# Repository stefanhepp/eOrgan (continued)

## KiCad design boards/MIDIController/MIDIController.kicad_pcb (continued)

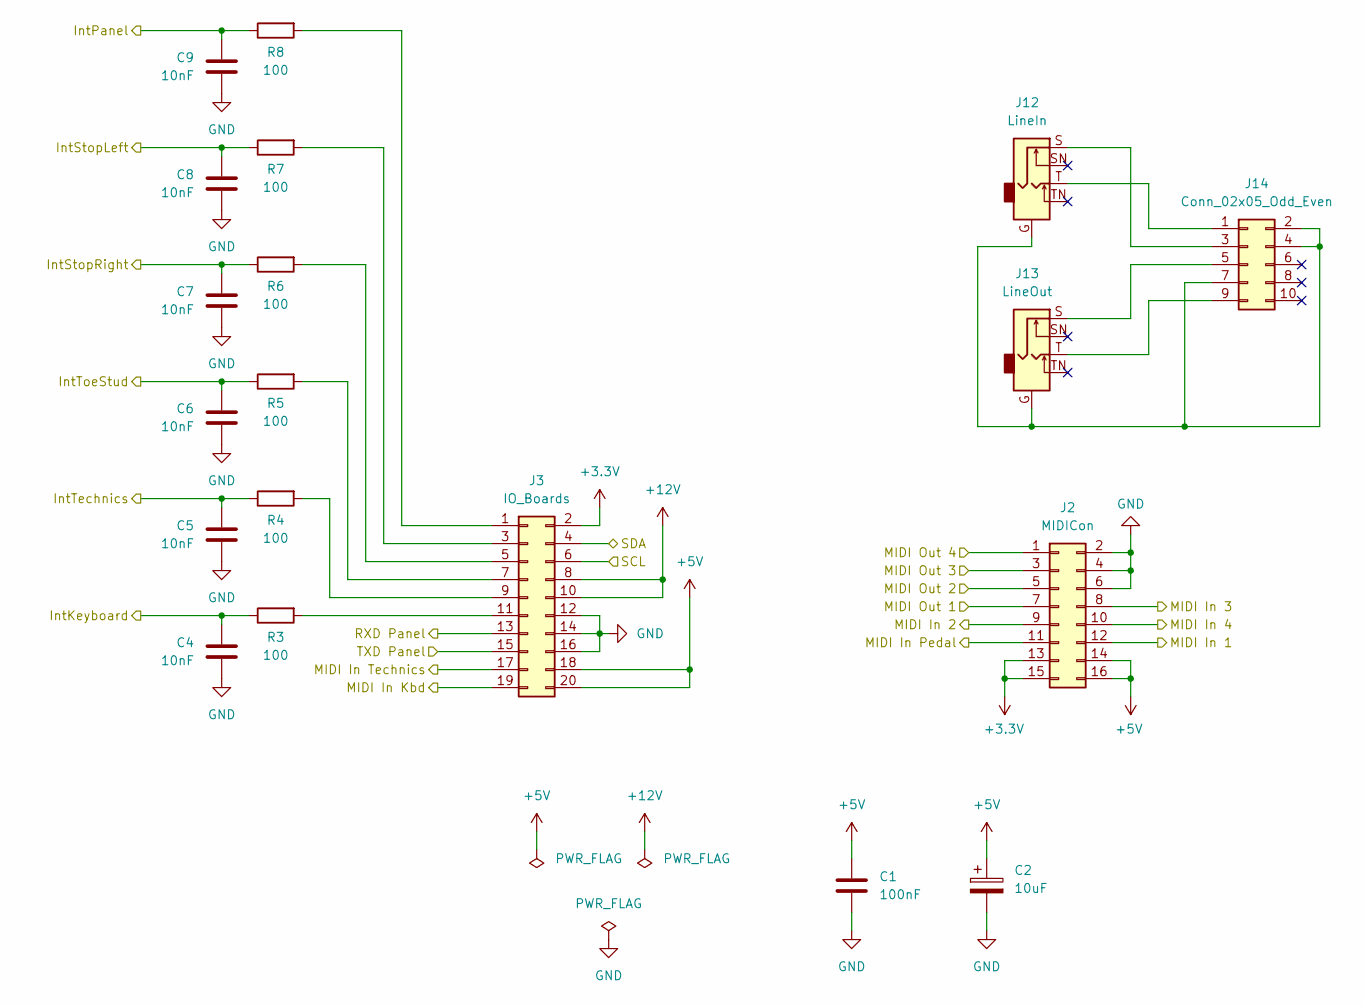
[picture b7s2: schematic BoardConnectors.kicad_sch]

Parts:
C1: 100nF; C_Disc_D4.3mm_W1.9mm_P5.00mm
C2: 10uF; CP_Radial_D5.0mm_P2.00mm
C4, C5, C6, C7, C8, C9: 10nF; C_Disc_D3.8mm_W2.6mm_P2.50mm
J2: MIDICon; IDC-Header_2x08_P2.54mm_Vertical
J3: IO_Boards; IDC-Header_2x10_P2.54mm_Vertical
J12: LineIn; Jack_3.5mm_Ledino_KB3SPRS_Horizontal_Stereo
J13: LineOut; Jack_3.5mm_Ledino_KB3SPRS_Horizontal_Stereo
J14: Conn_02x05_Odd_Even; PinHeader_2x05_P2.54mm_Vertical
R3, R4, R5, R6, R7, R8: 100; R_Axial_DIN0207_L6.3mm_D2.5mm_P10.16mm_Horizontal

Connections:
+3.3V: J2.13, J2.15, J3.2; also elsewhere on the board
+5V: C1.1, C2.1, J2.14, J2.16, J3.18, J3.20; also elsewhere on the board
+12V: J3.8, J3.10
/Int_Kbd: C4.1, R3.1; also elsewhere on the board
/Int_Panel: C9.1, R8.1; also elsewhere on the board
/Int_StopLeft: C8.1, R7.1; also elsewhere on the board
/Int_StopRight: C7.1, R6.1; also elsewhere on the board
/Int_Technics: C5.1, R4.1; also elsewhere on the board
/Int_ToeStud: C6.1, R5.1; also elsewhere on the board
/RXD1: J2.9; also elsewhere on the board
/RXD2: J3.19; also elsewhere on the board
/RXD3: J3.17; also elsewhere on the board
/RXD4: J2.10; also elsewhere on the board
/RXD5: J2.12; also elsewhere on the board
/RXD6: J3.13; also elsewhere on the board
/RXD7: J2.8; also elsewhere on the board
/RXD8: J2.11; also elsewhere on the board
/SCL: J3.6; also elsewhere on the board
/SDA: J3.4; also elsewhere on the board
/TXD1: J2.5; also elsewhere on the board
/TXD4: J2.1; also elsewhere on the board
/TXD5: J2.7; also elsewhere on the board
/TXD6: J3.15; also elsewhere on the board
/TXD7: J2.3; also elsewhere on the board
GND: C1.2, C2.2, C4.2, C5.2, C6.2, C7.2, C8.2, C9.2, J2.2, J2.4, J2.6, J3.12, J3.14, J3.16; also elsewhere on the board
unnamed: J3.1, R8.2
unnamed: J3.3, R7.2
unnamed: J3.5, R6.2
unnamed: J3.7, R5.2
unnamed: J3.9, R4.2
unnamed: J3.11, R3.2
unnamed: J12.T, J14.1
unnamed: J12.G, J13.G, J14.2, J14.4, J14.7
unnamed: J12.S, J14.3
unnamed: J13.S, J14.5
unnamed: J13.T, J14.9

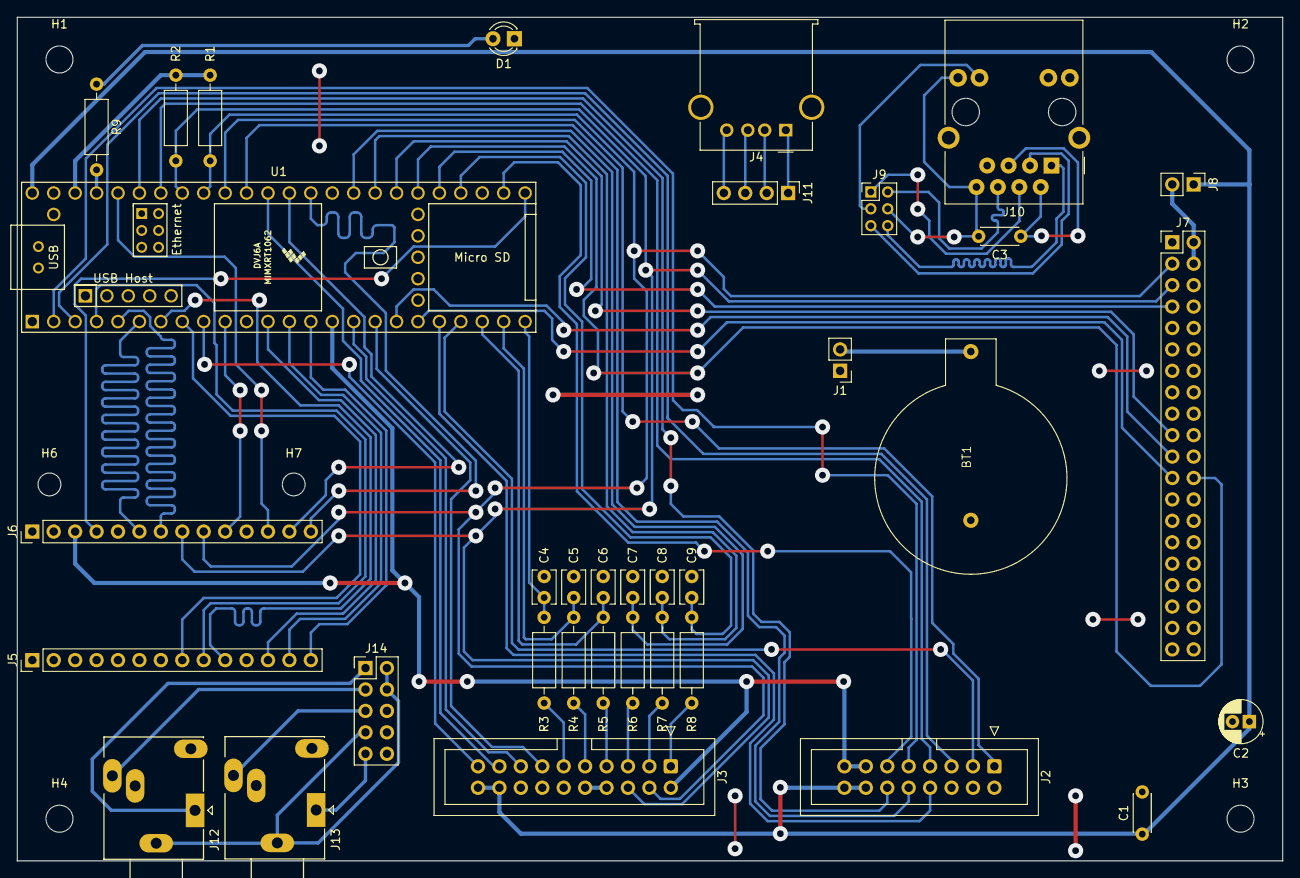
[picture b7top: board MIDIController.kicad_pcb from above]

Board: 2 copper layers, 150.0 x 100.0 mm, 41 parts (0 on the bottom side), 70 nets.

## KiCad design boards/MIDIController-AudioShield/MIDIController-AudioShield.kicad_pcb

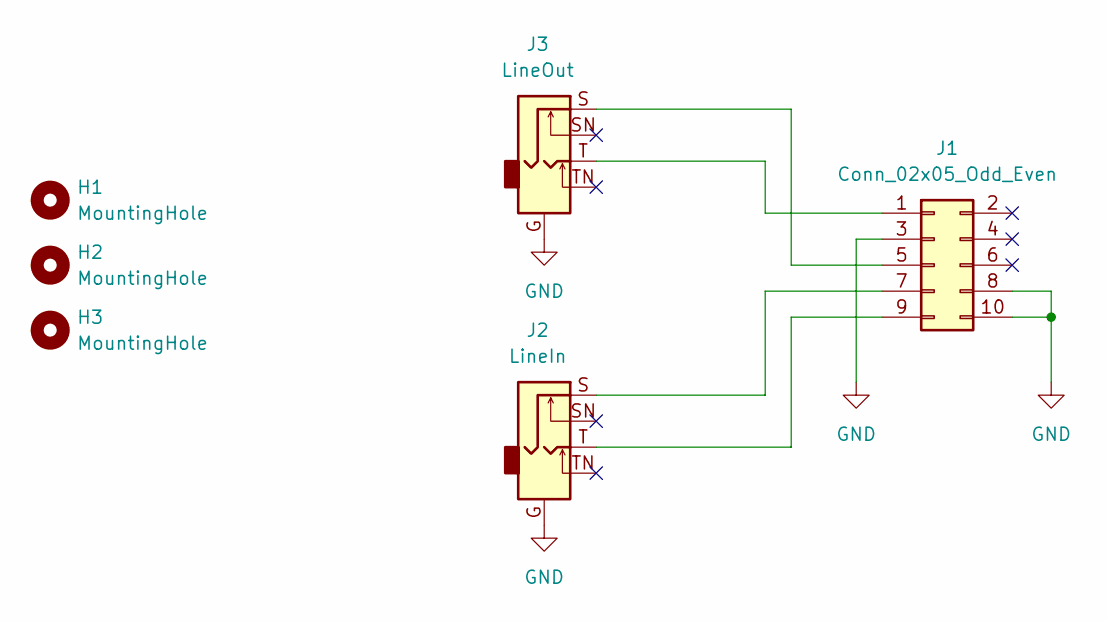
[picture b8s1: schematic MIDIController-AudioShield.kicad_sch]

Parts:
H1, H2, H3: MountingHole; MountingHole_3.2mm_M3
J1: Conn_02x05_Odd_Even; PinHeader_2x05_P2.54mm_Vertical
J2: LineIn; Jack_3.5mm_Ledino_KB3SPRS_Horizontal_Stereo
J3: LineOut; Jack_3.5mm_Ledino_KB3SPRS_Horizontal_Stereo

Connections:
GND: J1.3, J1.8, J1.10, J2.G, J3.G
unnamed: J1.1, J3.T
unnamed: J1.5, J3.S
unnamed: J1.7, J2.S
unnamed: J1.9, J2.T

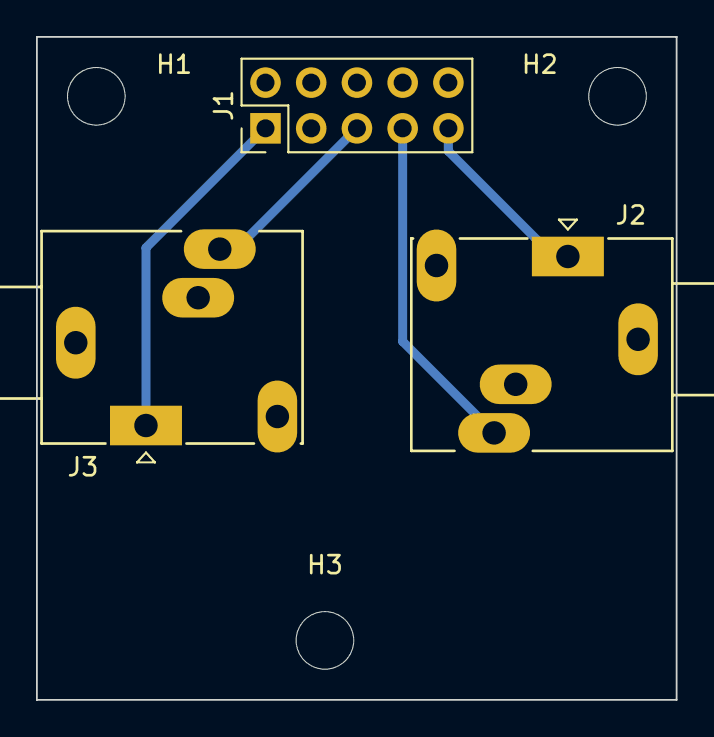
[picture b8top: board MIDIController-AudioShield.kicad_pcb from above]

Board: 2 copper layers, 35.5 x 36.8 mm, 6 parts (0 on the bottom side), 5 nets.

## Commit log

2013-10-13 Initial commit or encoder boards
2013-10-14 Added schematics of thumb pistons
2013-10-14 Fixed thumb piston wiring schematics
2013-10-14 First version of thumb encoder schematics
2013-10-15 Added first matrix encoder schematics, some design files
2013-10-15 Updated matrix encoder schematics
2022-09-15 Added old firmware and design files
2022-10-30 Initial design files for new Console design.
    Moved old design to archive folder, updated some documents for new
    design.
2022-11-13 New SwellEncoder schematics, updated MIDI paths in Boards diagram
2022-11-19 Added Freecad files for toestop switch holder and button boxes
2022-12-17 Updated 3D printed part designs and added STL exports
2022-12-17 Added Boutique retention hook design from https://www.thingiverse.com/thing:2430610
2022-12-17 Fixed Boutique retention hook design to fit Roland SE-02
2022-12-17 Renamed toestud encoder schematics
2022-12-17 Renamed toe stud connectors
2022-12-17 Renamed encoder boards and recreated with KiCAD 6
2022-12-18 Added schematics of pedal board controller
2022-12-18 Some updates to piston encoder schematics
2022-12-20 Updated Pedal Encoder to use UART from ToeStudEncoder
2022-12-20 Added Keyboard encoder and Midi encoder design using shift registers
2022-12-20 Finished Piston encoder schematics
2022-12-21 Updated keyboard encoder to use 8-1 Mux instead of shift registers
2022-12-21 Annoted ICs
2022-12-21 Added base schematics for Technics keyboard encoder
2022-12-21 Updated Board overview diagrams for new keyboard encoders
2022-12-21 Added initial schematics for main controller board
2023-02-22 Moved firmware sources to separate repository
2023-02-22 Using Creative Commons 4.0 ShareAlike license for hardware design
2023-02-22 Fixed readme formatting
2023-04-17 Remove temporary and local KiCAD files
2023-04-19 Renamed PCBs and updated to KiCAD 7.0
2023-04-19 Moved individual part designs into subfolder
2023-04-23 Created new signals drawings
2023-10-21 Added Audio/MIDI routes diagram
2023-10-21 PCB layout for keyboard scanner and piston encoder
2024-01-13 Ignore new freecad backup files
2024-01-13 Added redesigned Roland Boutique holder
2024-02-07 Added Audio frontpanel, added more MIDI ports to controller
2024-02-13 Added output buffer to MIDI outputs
2024-03-04 Updated to KiCAD 8, fixed optocouplers for MIDI and added powersupplies
2024-03-04 New PCB version of PedalEncoder
2024-03-05 Using custom TO220 cooler, fixed and finished several PCBs
2024-03-05 Finished PCB for ToeStudEncoder
2024-03-06 Cleanup of PCB sizes and mounthole positions. Moved MIDI connectors to separate board.
2024-03-06 Finished PCB for MIDI IO board
2024-03-07 Added Optocoupler and RS232 converter to UART board lines.
2024-03-08 Finished IO-Board PCB, switched RX/TX of board connectors for better routing
2024-03-08 Finished connectors on MIDIController board, fixed 3.3V IO voltage levels
2024-03-08 Updated MidiController PCB footprints
2024-03-11 Fixed interrupt line to use open collector, added pullups to I2C lines
2024-03-11 Added CR2032 holder footprint, allow routing between pins
2024-03-13 Added bypass caps to power supplies, use cheaper MAX232 IC.
2024-05-18 Updated design rules to 0.32mm template and exported Gerber files
2024-06-16 Fixed some RX/TX pin swaps
2024-06-16 Initial firmware commands doc
2024-06-17 Added notes on MIDI and I2C routing and opcodes
2024-06-26 Fixed size of I2C expander board footprint
2024-06-30 Added PCB holder model
2024-06-30 Make Toestud PS2 connectors symmetrical to avoid connection errors
2024-06-30 Added case for ToeStudEncoder
2024-06-30 ToeStudEncoder: Fixed mirrored PS2 pinout
2024-06-30 Added slide-in holder for ToeStudEncoder case
2024-07-03 Fixed mirrored MIDI board connector
2024-07-04 Updated I2C protocol
2024-07-10 Fixed Piston wiring schematics, updated I2C message formats
2024-07-21 Added software architecture overview for MIDIcontroller
2024-07-21 Updated I2C message formats
2024-07-23 Updated I2C message formats and SW arhitecture
2024-08-03 Fixed PedalEncoder ISP hedaer schematics, added Errata notes
2024-08-05 Fixed PedalEncoder ISP connections
2024-08-18 Moved firmware docs to eOrgan-firmware repo
2024-08-30 Fixed KeyboardScanner schematics to fix open collector enable output
2024-08-31 Revert "Fixed KeyboardScanner schematics to fix open collector enable output"
    This reverts commit 57decbb2314c6d76a4ad6cd92ca682e4977913ef.
2024-08-31 Replaced inverting with non-inverting output buffer in KeyboardScanner to fix disabled open collector output
2024-08-31 Reverting to using 2803A inverted open collector for Keyboard Scanner, fixed layout
2024-09-02 Added IDC16 connector workaround, PCB holder for TechnicsEncoder
2024-09-02 Added LED controller board
2024-09-07 Exported LEDController gerber
2024-09-07 Parametric design for PCB holder
2024-09-07 Fixed LEDController button header layout
2024-09-13 Revert "Replaced inverting with non-inverting output buffer in KeyboardScanner to fix disabled open collector output"
    This reverts commit 6ddf25a0a7a31b9f16f3f110cd3b7ae66d122c97.
2024-09-13 Fixed pulldown resistors for KeyboardScanner
2024-09-13 Revert "Reverting to using 2803A inverted open collector for Keyboard Scanner, fixed layout"
    This reverts commit 7b46a6886eac97662925cbadd02de0ff96663bd2.
2024-10-05 Initial interface plan
2024-10-08 Added keyboard locking mount model, initial Line audioshield board
2024-10-08 Finished design of AudioShield
2024-10-08 Fixed swapped I2S data lines in schematics
2024-10-08 Fixed MIDIController I2S PCB, added LED
2024-10-11 Added line jacks for the audio board.
2024-10-13 Added initial panel breakout board schematics
2024-10-17 Initial schematics for panel control boards
2024-10-18 Added panel design files and panel schematics
2024-10-20 Finished PCB layouts for panel keypad
2024-10-21 Added keycap variants
2024-10-24 Added grbl jobs for panel cutouts
2024-10-30 Added 3d parts for music stand, display holder
2024-10-30 Updated LED resistor values
2024-10-30 Fixed using 5V from main power for PWR LED
2024-11-02 Fixes for missing pullups on keypad buttons
2024-11-02 Updated panel breakout board to use second I2C to avoid conflict with display
2024-11-02 Fixed missing I2C pullup for Raspberry I2C-0
2024-11-03 Moved panels dia drawing to archive
2024-11-07 Disconnected UART lines to avoid interference
